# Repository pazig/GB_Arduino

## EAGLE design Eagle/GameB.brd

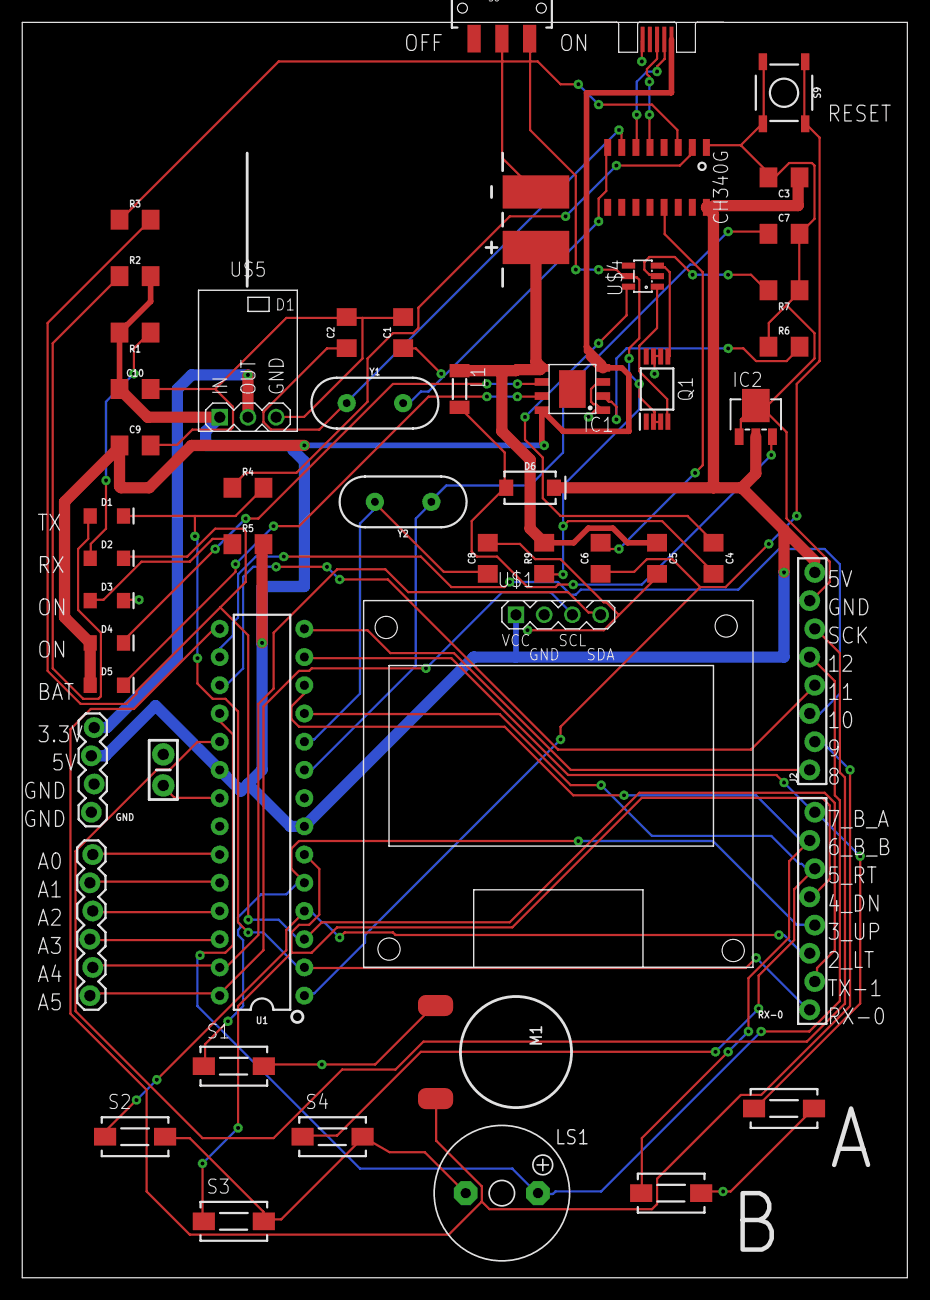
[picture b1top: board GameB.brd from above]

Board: 2 copper layers, 79.7 x 113.0 mm, 52 parts (0 on the bottom side), 49 nets.

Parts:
BT1: 6.8MM_COIN_CELL; LIPO-110-TABS
C1, C2: 22p; 1206
C3, C10: 12uF; 1206
C4, C6: 100nF; 1206
C5: 10uF; 1206
C7, C8: 22pF; 1206
C9: 0.1p; 1206
C11: 0.1uF; CAP-PTH-SMALL-KIT
D1, D2: YELLOW; LED-1206
D3, D4: GREEN; LED-1206
D5: RED; LED-1206
D6: 1A/40V/500mV; SMA-DIODE
GND: 1X04_LOCK
IC1: TP4056; SOP-8
IC2: L78LXXCU/BU; SOT89
J2: 1X08_FEMALE_LOCK
J3: 1X06_LOCK
L1: 22uH; SM-1206
LS1: F/QMX
M1: MOTORSHORT; VIBE-MOTOR-10MM-SMD
Q1: FS8205A; SOP65P640X120-8N
R1, R2, R3, R4, R5, R7, R9: 1k; 1206
R6: 1.2k; 1206
RX-0: 1X08_FEMALE_LOCK
S1, S2, S3, S4, S5, S6: DTSM-3
S8: SWITCH_SPDT_SMD
S9: MOMENTARY-SWITCH-SPST-SMD-5.2-REDUNDANT; TACTILE_SWITCH_SMD_5.2MM
U1: 328P; DIP28
U$1: DISPLAY-OLED-128X64-I2C
U$2: CH340G; SOIC16
U$3: PCB_MICRO_USB_BSS_1; USB_TYPE_B_SS_1
U$4: DW01A; SOT23-6
U$5: REG-AMS1117-3P-3.3V; REG-AMS1117-3P
Y1: 12000; HC49US
Y2: 16MHz; HC49US

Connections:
2: RX-0.3, S2.1, U1.4
3: RX-0.4, S1.1, U1.5
3.3V: GND.4, U$5.2
4: RX-0.5, S3.1, U1.6
5: RX-0.6, S4.1, U1.11
5V: C3.1, C10.1, D6.C, GND.3, IC2.2, J2.8, R1.2, R2.2, R5.2, U1.7, U1.20, U$1.1, U$2.16, U$5.1
6: RX-0.7, S5.1, U1.12
7: RX-0.8, S6.1, U1.13
8: J2.1, U1.14
9: J2.2, M1.+, U1.15
A0: J3.1, U1.23
A1: J3.2, U1.24
A2: J3.3, U1.25
A3: J3.4, U1.26
A4: J3.5, U1.27, U$1.4
A5: J3.6, U1.28, U$1.3
GND: C1.2, C2.2, C3.2, C5.2, C7.2, C8.2, C9.2, C10.2, C11.2, D3.C, GND.1, GND.2, IC1.1, IC1.3, IC2.1, IC2.4, J2.7, LS1.-, M1.-, Q1.6, Q1.7, R6.1, R7.1, S1.2, S2.2, S3.2, S4.2, S5.2, S6.2, S9.3, S9.4, U1.8, U1.22, U$1.2, U$2.1, U$3.1, U$5.3
MISO: J2.5, LS1.+, U1.18
MOSI: J2.4, U1.17
unnamed: U$2.6, U$3.4
unnamed: U$2.5, U$3.3
unnamed: D2.A, R1.1
unnamed: D1.A, R2.1
unnamed: C1.1, U$2.8, Y1.2
unnamed: C2.1, U$2.7, Y1.1
unnamed: BT1.+, C5.1, IC1.5, L1.1, R9.2
unnamed: R3.1, U$2.3
unnamed: R4.1, U$2.2
unnamed: D3.A, R5.1
unnamed: D6.A, IC2.3, L1.2
unnamed: D4.C, IC1.6
unnamed: IC1.2, R6.2
unnamed: C9.1, D4.A, D5.A, IC1.4, IC1.8, U$3.5
unnamed: D5.C, IC1.7
unnamed: C6.2, U$2.13
unnamed: R7.2, U$4.2
unnamed: Q1.5, U$4.3
unnamed: Q1.4, U$4.1
unnamed: C4.2, Q1.2, Q1.3, R9.1, S8.3, U$4.5
unnamed: C4.1, U$4.6
unnamed: BT1.-, S8.2
unnamed: C6.1, S9.1, S9.2, U1.1
unnamed: C7.1, U1.9, Y2.1
unnamed: C8.1, U1.10, Y2.2
unnamed: C11.1, U1.21
RX0: D1.C, R4.2, RX-0.1, U1.2
SCK: J2.6, U1.19
SS: J2.3, U1.16
TX1: D2.C, R3.2, RX-0.2, U1.3

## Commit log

2020-10-15 final

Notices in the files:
parts and their libraries:
SparkFun-Retired: Licensing: Creative Commons ShareAlike 4.0 International - https://creativecommons.org/licenses/by-sa/4.0
diy-modules: Released under the Creative Commons Attribution 4.0 International License: http://creativecommons.org/licenses/by/4.0
